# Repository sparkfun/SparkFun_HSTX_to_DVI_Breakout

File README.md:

SparkFun HSTX to DVI Breakout
========================================

[*SparkFun HSTX to DVI Breakout  (BOB-28468)*](https://www.sparkfun.com/sparkfun-hstx-to-dvi-breakout.html)

The SparkFun HSTX to DVI Breakout takes the 22-pin interface found on the HSTX connector on the IoT RedBoard - RP2350 as well as the camera and display connectors on a Rasbperry Pi 5 and translates it to an HDMI connector for DVI output.

The board includes a 22-pin flex cable connector and HDMI connector along with the required components to level shift and boost the voltage for compatability with DVI signal requirements.

Repository Contents
-------------------

* **/Hardware** - Eagle design files (.brd, .sch)

Product Versions
----------------
* [BOB-28468](https://www.sparkfun.com/sparkfun-hstx-to-dvi-breakout.html) - HSTX to DVI Breakout for the RedBoard IoT - RP2350.

License Information
-------------------

This product is _**open source**_! 

Please review the LICENSE.md file for license information. 

If you have any questions or concerns on licensing, please contact technical support on our [SparkFun forums](https://forum.sparkfun.com/viewforum.php?f=152).

Distributed as-is; no warranty is given.

- Your friends at SparkFun.

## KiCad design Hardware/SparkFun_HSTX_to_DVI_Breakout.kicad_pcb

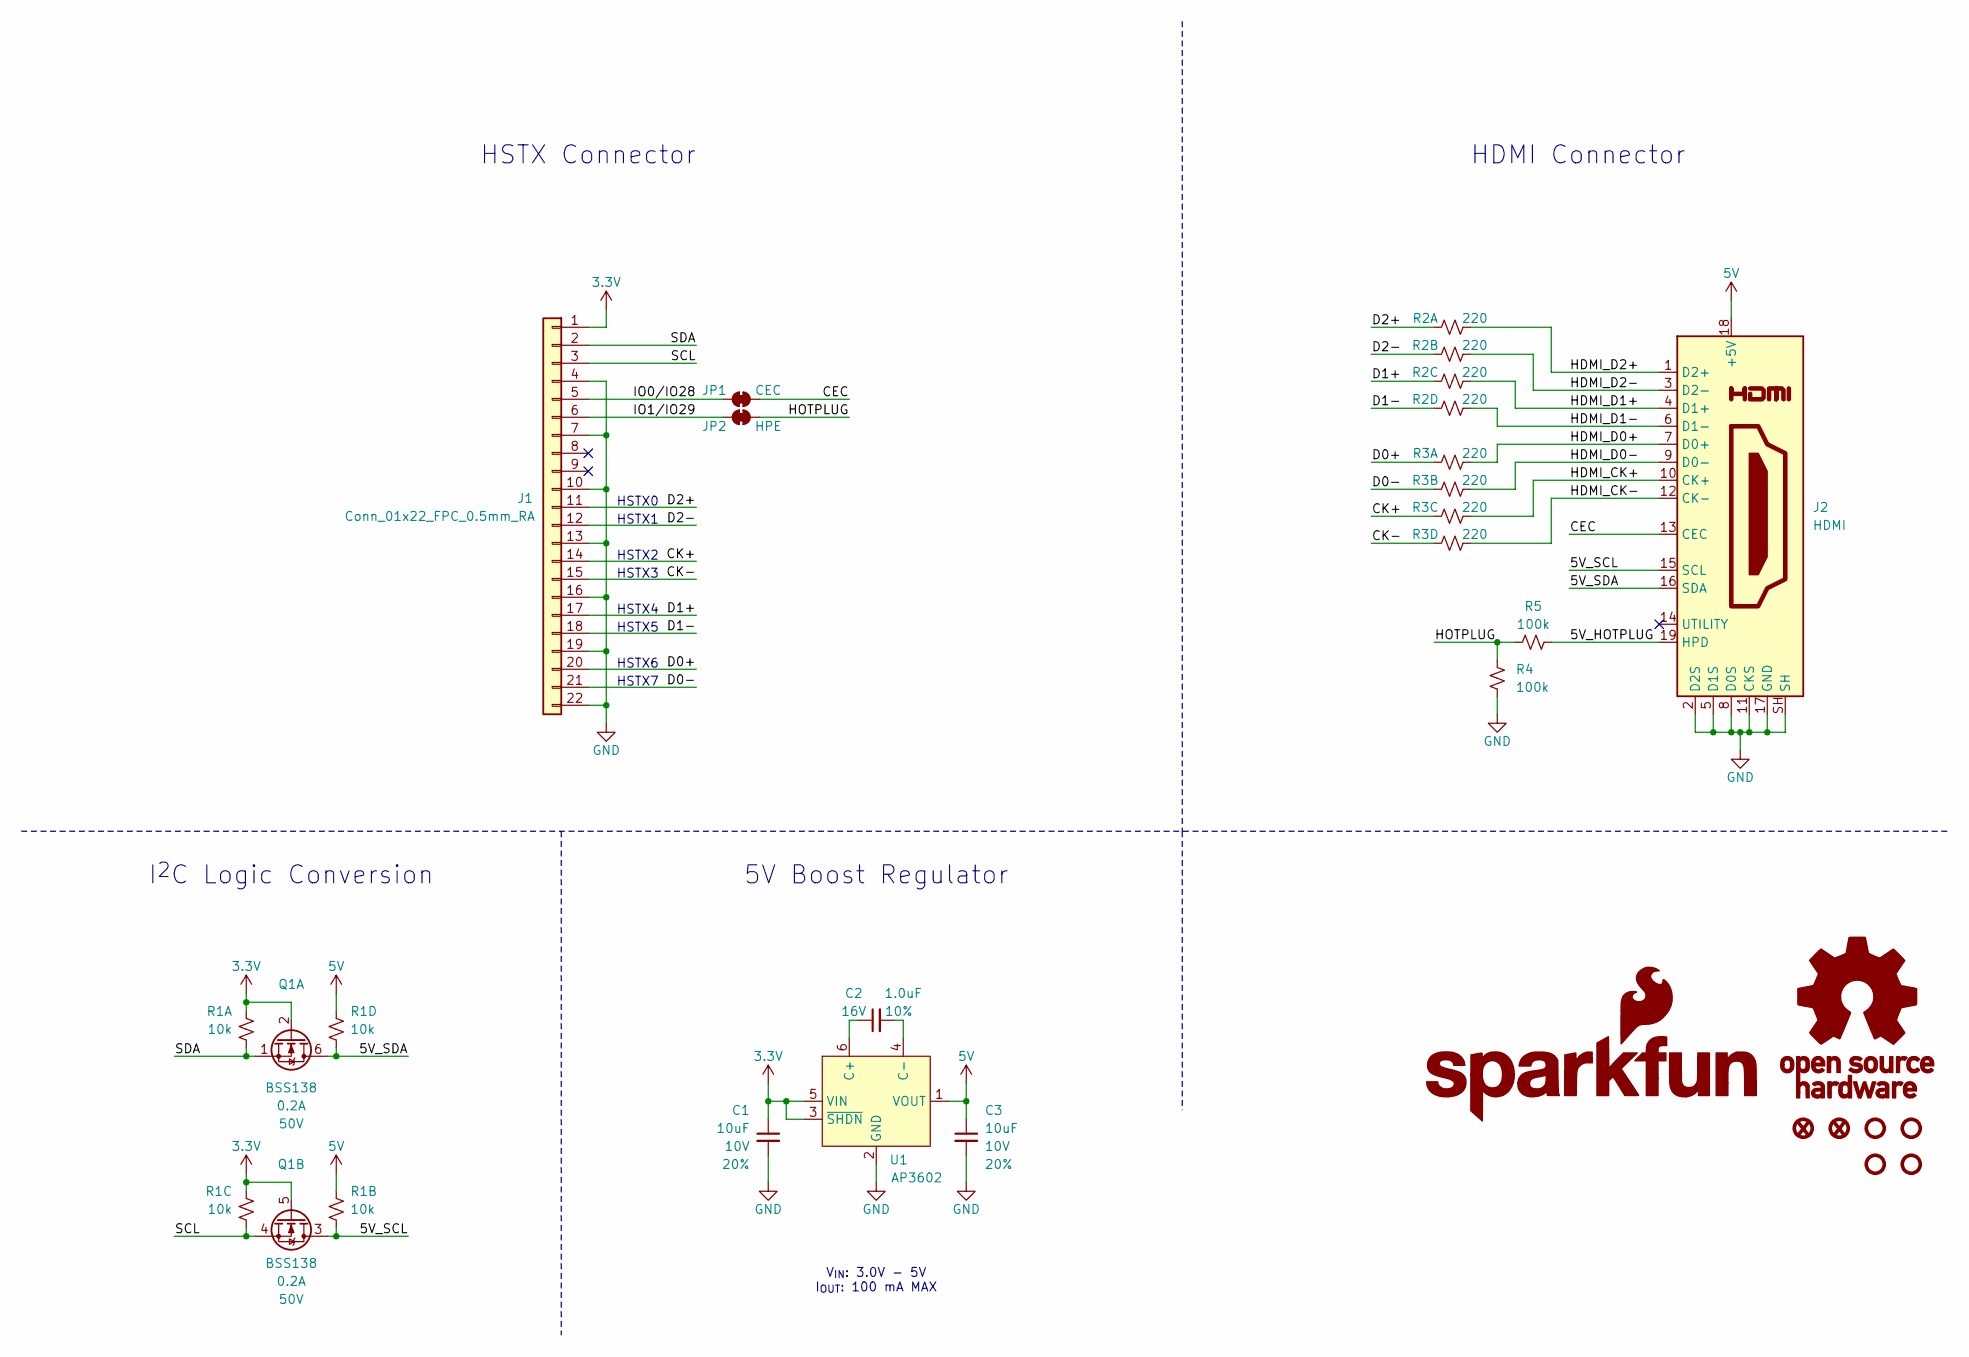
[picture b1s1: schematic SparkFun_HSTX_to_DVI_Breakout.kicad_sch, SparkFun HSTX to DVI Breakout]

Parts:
C1, C3: 10uF; C_0603_1608Metric; Voltage 10V; Tolerance 20%
C2: 1.0uF; C_0603_1608Metric; Voltage 16V; Tolerance 10%
FID1, FID2: Fiducial_0.5mm; Fiducial_0.5mm_Mask1mm
G1: SparkFun_Logo
G2: OSHW_Logo; Creative_Commons_License
J1: Conn_01x22_FPC_0.5mm_RA; FPC_0.5mm-22_RA
J2: HDMI; HDMI_A_19P_SMD
JP1: CEC; Jumper_2_NC_Trace
JP2: HPE; Jumper_2_NC_Trace
Q1: BSS138; SOT-363
R1: 10k; R_1206_Array_Convex
R2, R3: 220; R_0804_Array_Convex
R4, R5: 100k; R_0402_1005Metric
ST1, ST2, ST3, ST4: Standoff
U1: AP3602; SOT23-6

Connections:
3.3V: C1.1, J1.1, Q1.2 (G), Q1.5 (G), R1.2, R1.6, U1.3 (~SHDN), U1.5 (VIN)
5V: C3.1, J2.18 (+5V), R1.4, R1.8, U1.1 (VOUT)
/5V_HOTPLUG: J2.19 (HPD), R5.2
/5V_SCL: J2.15 (SCL), Q1.3 (D), R1.3
/5V_SDA: J2.16 (SDA), Q1.6 (D), R1.7
/CEC: J2.13 (CEC), JP1.2 (B)
/CK+: J1.14, R3.5
/CK-: J1.15, R3.7
/D0+: J1.20, R3.1
/D0-: J1.21, R3.3
/D1+: J1.17, R2.5
/D1-: J1.18, R2.7
/D2+: J1.11, R2.1
/D2-: J1.12, R2.3
/HDMI_CK+: J2.10 (CK+), R3.6
/HDMI_CK-: J2.12 (CK-), R3.8
/HDMI_D0+: J2.7 (D0+), R3.2
/HDMI_D0-: J2.9 (D0-), R3.4
/HDMI_D1+: J2.4 (D1+), R2.6
/HDMI_D1-: J2.6 (D1-), R2.8
/HDMI_D2+: J2.1 (D2+), R2.2
/HDMI_D2-: J2.3 (D2-), R2.4
/HOTPLUG: JP2.2 (B), R4.1, R5.1
/IO0/IO28: J1.5, JP1.1 (A)
/IO1/IO29: J1.6, JP2.1 (A)
/SCL: J1.3, Q1.4 (S), R1.5
/SDA: J1.2, Q1.1 (S), R1.1
GND: C1.2, C3.2, J1.4, J1.7, J1.10, J1.13, J1.16, J1.19, J1.22, J2.2 (D2S), J2.5 (D1S), J2.8 (D0S), J2.11 (CKS), J2.17 (GND), J2.SH, R4.2, U1.2 (GND)
unnamed: C2.1, U1.6 (C+)
unnamed: C2.2, U1.4 (C-)

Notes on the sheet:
5V Boost Regulator
HDMI Connector
HSTX3
HSTX0
HSTX5
HSTX Connector
HSTX2
HSTX4
I^{2}C Logic Conversion
V_{IN}: 3.0V - 5V I_{OUT}: 100 mA MAX
HSTX7
HSTX6
HSTX1

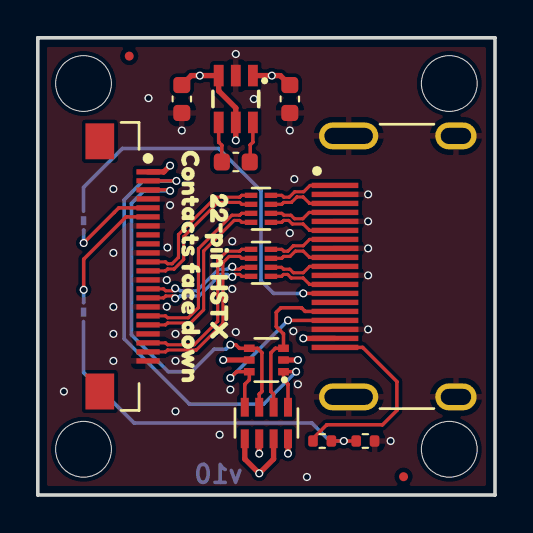
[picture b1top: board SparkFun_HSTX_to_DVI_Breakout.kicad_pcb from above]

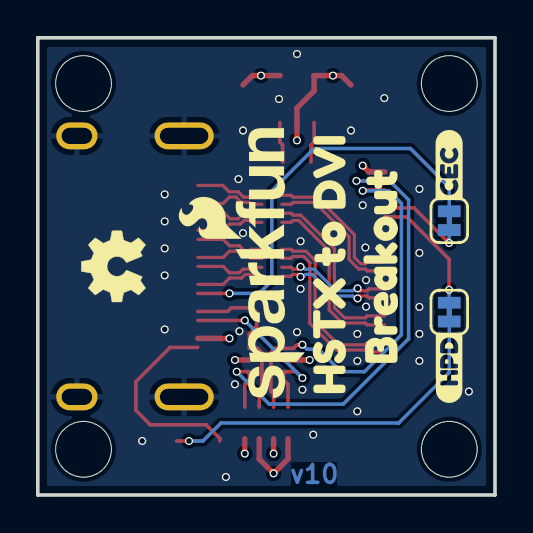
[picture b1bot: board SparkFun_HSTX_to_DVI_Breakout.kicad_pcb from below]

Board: 4 copper layers, 25.4 x 25.4 mm, 28 parts (7 on the bottom side), 30 nets.

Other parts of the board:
Ref**: Val**; OSHW_Logo_4mm
kibuzzard-67C21FDF: G***; kibuzzard-67C21FDF
kibuzzard-67C220EB: G***; kibuzzard-67C220EB
kibuzzard-67C223E4: G***; kibuzzard-67C223E4
kibuzzard-67C2232E: G***; kibuzzard-67C2232E
kibuzzard-67C22006: G***; kibuzzard-67C22006
kibuzzard-67C22392: G***; kibuzzard-67C22392

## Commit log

2025-03-03 Add design files for review
2025-03-03 Update SparkFun_HSTX_to_DVI_Breakout.kicad_pcb
    Add Impedance control to Ordering instructions
2025-03-03 Add dates
2025-03-03 Update prod_id
2025-03-04 Design review updates
    Fix wandering measure.
    Move 5V trace to avoid splitting 3.3V vias.
    Add more ground vias.
    Delete unused README.
2025-03-27 Update README.md
    Updating readme from template to add photos, hyperlinks & short description.
2025-04-01 Update README
    Adding banner photo & updating README photo link.

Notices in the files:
parts and their libraries:
Released under the Creative Commons Attribution Share-Alike 4.0 License
https://creativecommons.org/licenses/by-sa/4.0
